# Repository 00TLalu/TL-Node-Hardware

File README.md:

# TL-Node-Hardware
 PCB for OpenTANI

## Spesification
- TL-S2 (ESP32-S2)
- 2 External LDO
- 6 port 4 pin JST-PH Sensor
- 1 port 2 pin JST-PH Battery
- 1 port 2 pin JST-SH Buzzer
- 1 port 4 pin JST-SH I2C
- 1 port 6 pin JST-SH UART
- 1 port 6 pin JST-SH JTAG/SPI
- 2 Reed Switch
- 2 pcs Battery 18650 Battery
- 1 Programeble LED
- 1 Power Switch
- Voltage/Battery Monitor
- MPU-6050 (Optional)

## Schematic

## 3D Model

## PCB

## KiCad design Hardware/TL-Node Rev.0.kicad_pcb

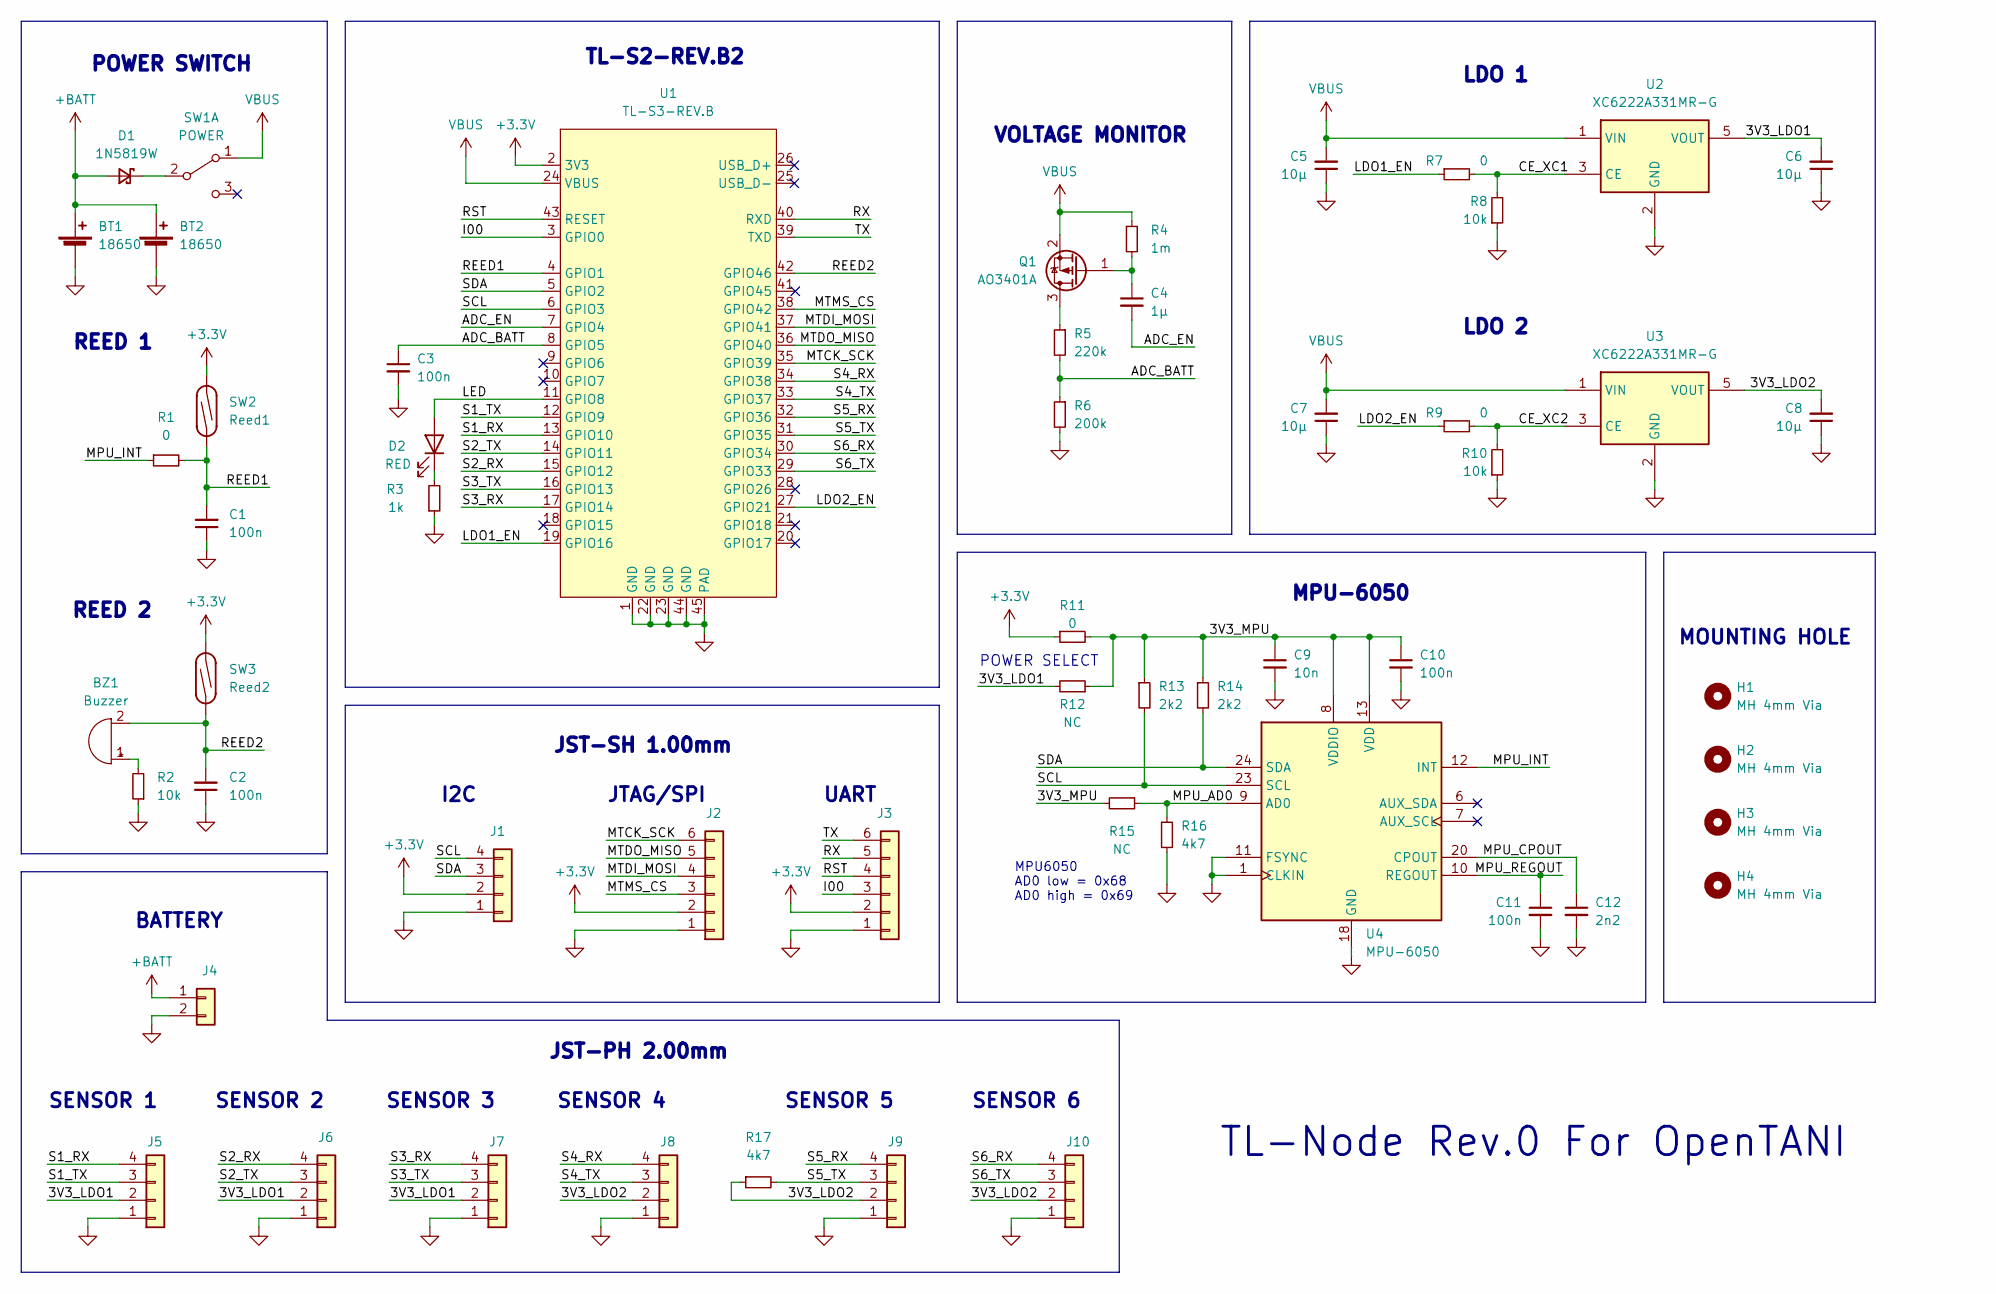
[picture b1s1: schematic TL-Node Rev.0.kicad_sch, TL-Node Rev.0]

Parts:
BT1, BT2: 18650; BatteryHolder_MPD_BH-18650-PC2
BZ1: Buzzer; JST_SH_BM02B-SRSS-TB_1x02-1MP_P1.00mm_Vertical
C1, C2, C3, C10, C11: 100n; C_0402_TL
C4: 1µ; C_0402_TL
C5, C6, C7, C8: 10µ; C_0603_TL
C9: 10n; C_0402_TL
C12: 2n2; C_0402_TL
D1: 1N5819W; D_SOD-123F
D2: RED; D_0603_TL
H1, H2, H3, H4: MH 4mm Via; MountingHole_3mm_Pad_Via
J1: JST-PH 1x04; JST_SH_BM04B-SRSS-TB_1x04-1MP_P1.00mm_Vertical_TL
J2, J3: JST-SH 1x06; JST_SH_1x06-1MP_P1.00mm_Vertical_TL
J4: JST-PH 1x02; JST_PH_B2B-PH-TL-2.0
J5, J6, J7, J8, J9, J10: JST-PH 1x04; JST_PH_S4B-PH-SM4-TB_1x04-1MP_P2.00mm_Horizontal
Q1: AO3401A; SOT-23_TL
R1, R7, R9, R11: 0; R_0402_TL
R2, R8, R10: 10k; R_0402_TL
R3: 1k; R_0402_TL
R4: 1m; R_0402_TL
R5: 220k; R_0402_TL
R6: 200k; R_0402_TL
R12, R15: NC; R_0402_TL
R13, R14: 2k2; R_0402_TL
R16, R17: 4k7; R_0402_TL
SW1: POWER; SW_SPDT_PCM12_TL
SW2: Reed1; SW_SPST_REED_CT10-XXXX-G1
SW3: Reed2; SW_SPST_REED_CT10-XXXX-G1
U1: TL-S3-REV.B; TL-S2_Rev.B2
U2, U3: XC6222A331MR-G; SOT-23-5_TL
U4: MPU-6050; InvenSense_QFN-24_4x4mm_P0.5mm_NoMask

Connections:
+3.3V: J1.2, J2.2, J3.2, R11.1, SW2.1, SW3.1, U1.2 (3V3)
+BATT: BT1.1 (+), BT2.1 (+), D1.2 (A), J4.1
/3V3_LDO1: C6.2, J5.2, J6.2, J7.2, R12.2, U2.5 (VOUT)
/3V3_LDO2: C8.2, J8.2, J9.2, J10.2, R17.1, U3.5 (VOUT)
/3V3_MPU: C9.1, C10.1, R11.2, R12.1, R13.1, R14.1, R15.2, U4.8 (VDDIO), U4.13 (VDD)
/ADC_BATT: C3.1, R5.2, R6.1, U1.8 (GPIO5)
/ADC_EN: C4.2, U1.7 (GPIO4)
/I00: J3.3, U1.3 (GPIO0)
/LDO1_EN: R7.1, U1.19 (GPIO16)
/LDO2_EN: R9.1, U1.27 (GPIO21)
/LED: D2.2 (A), U1.11 (GPIO8)
/MPU_AD0: R15.1, R16.1, U4.9 (AD0)
/MPU_CPOUT: C12.1, U4.20 (CPOUT)
/MPU_INT: R1.1, U4.12 (INT)
/MPU_REGOUT: C11.1, U4.10 (REGOUT)
/MTCK_SCK: J2.6, U1.35 (GPIO39)
/MTDI_MOSI: J2.4, U1.37 (GPIO41)
/MTDO_MISO: J2.5, U1.36 (GPIO40)
/MTMS_CS: J2.3, U1.38 (GPIO42)
/REED1: C1.2, R1.2, SW2.2, U1.4 (GPIO1)
/REED2: BZ1.2 (+), C2.2, SW3.2, U1.42 (GPIO46)
/RST: J3.4, U1.43 (RESET)
/RX: J3.5, U1.40 (RXD)
/S1_RX: J5.4, U1.13 (GPIO10)
/S1_TX: J5.3, U1.12 (GPIO9)
/S2_RX: J6.4, U1.15 (GPIO12)
/S2_TX: J6.3, U1.14 (GPIO11)
/S3_RX: J7.4, U1.17 (GPIO14)
/S3_TX: J7.3, U1.16 (GPIO13)
/S4_RX: J8.4, U1.34 (GPIO38)
/S4_TX: J8.3, U1.33 (GPIO37)
/S5_RX: J9.4, U1.32 (GPIO36)
/S5_TX: J9.3, R17.2, U1.31 (GPIO35)
/S6_RX: J10.4, U1.30 (GPIO34)
/S6_TX: J10.3, U1.29 (GPIO33)
/SCL: J1.4, R13.2, U1.6 (GPIO3), U4.23 (SCL)
/SDA: J1.3, R14.2, U1.5 (GPIO2), U4.24 (SDA)
/TX: J3.6, U1.39 (TXD)
GND: BT1.2 (-), BT2.2 (-), C1.1, C2.1, C3.2, C5.1, C6.1, C7.1, C8.1, C9.2, C10.2, C11.2, C12.2, J1.1, J2.1, J3.1, J4.2, J5.1, J6.1, J7.1, J8.1, J9.1, J10.1, R2.1, R3.1, R6.2, R8.1, R10.1, R16.2, U1.1 (GND), U1.22 (GND), U1.23 (GND), U1.44 (GND), U1.45 (PAD), U2.2 (GND), U3.2 (GND), U4.1 (CLKIN), U4.11 (FSYNC), U4.18 (GND)
unnamed: BZ1.1 (-), R2.2
unnamed: C4.1, Q1.1 (G), R4.2
unnamed: D1.1 (K), SW1.2 (B)
unnamed: D2.1 (K), R3.2
unnamed: Q1.3 (D), R5.1
unnamed: R7.2, R8.2, U2.3 (CE)
unnamed: R9.2, R10.2, U3.3 (CE)
VBUS: C5.2, C7.2, Q1.2 (S), R4.1, SW1.1 (A), U1.24 (VBUS), U2.1 (VIN), U3.1 (VIN)

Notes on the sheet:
LDO 2
TL-S2-REV.B2
SENSOR 4
TL-Node Rev.0 For OpenTANI
SENSOR 5
SENSOR 6
MPU-6050
VOLTAGE MONITOR
REED 1
JTAG/SPI
MOUNTING HOLE
SENSOR 3
MPU6050 AD0 low = 0x68 AD0 high = 0x69
UART
REED 2
BATTERY
POWER SWITCH
JST-PH 2.00mm
JST-SH 1.00mm
SENSOR 1
I2C
POWER SELECT
LDO 1
SENSOR 2

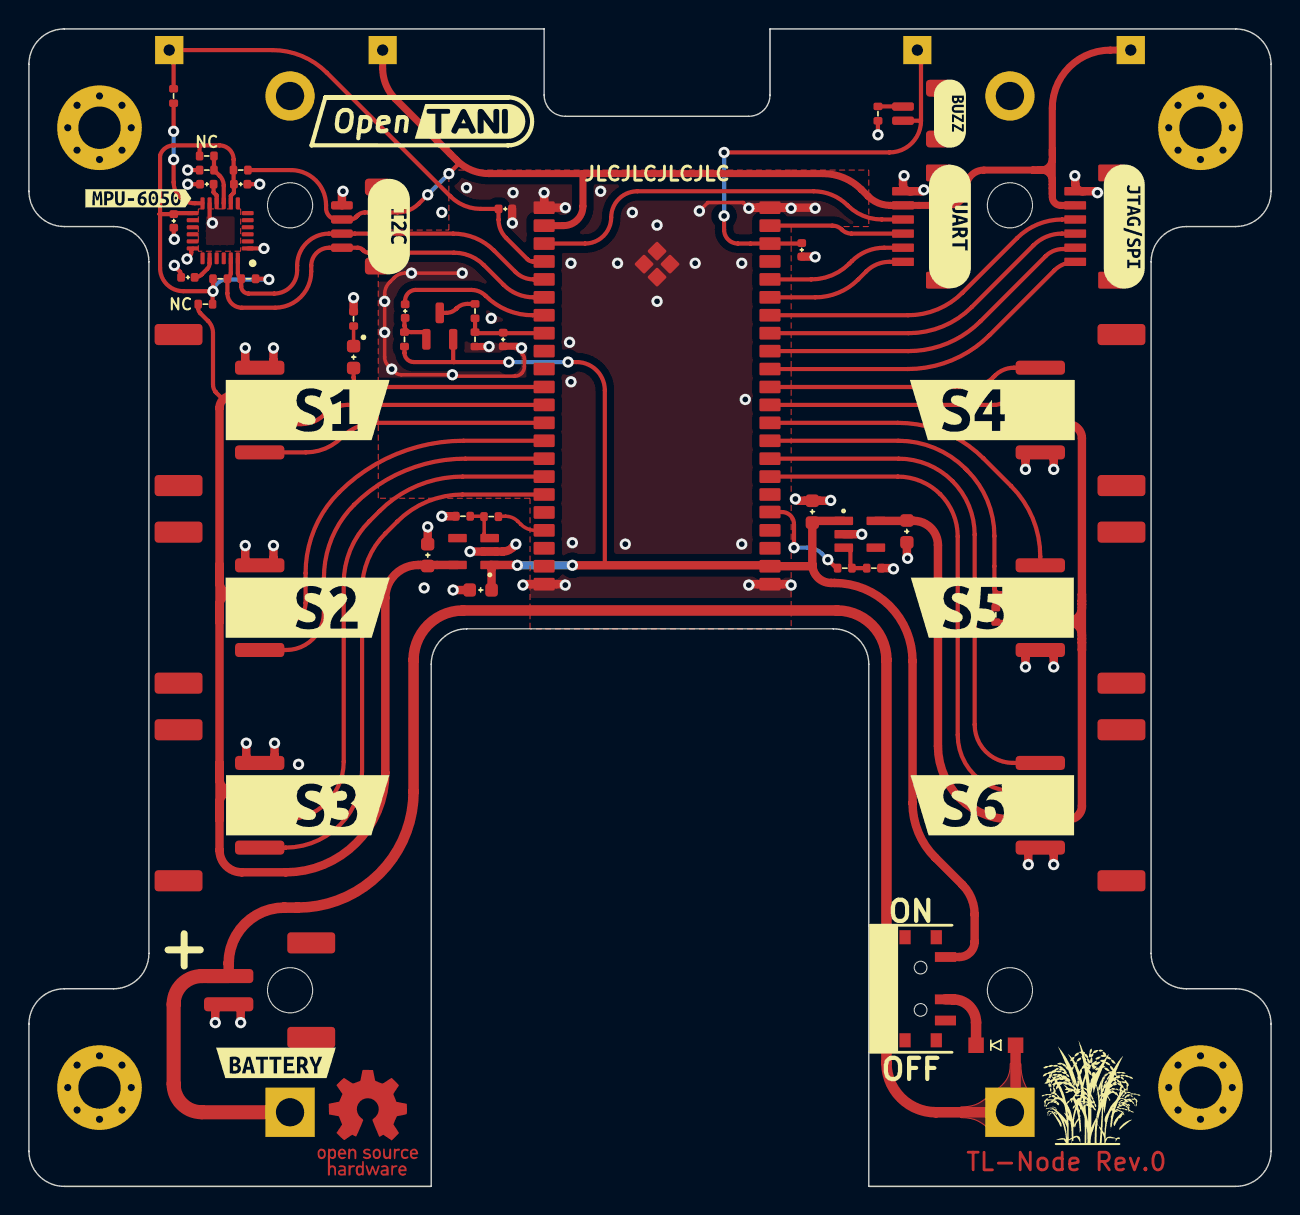
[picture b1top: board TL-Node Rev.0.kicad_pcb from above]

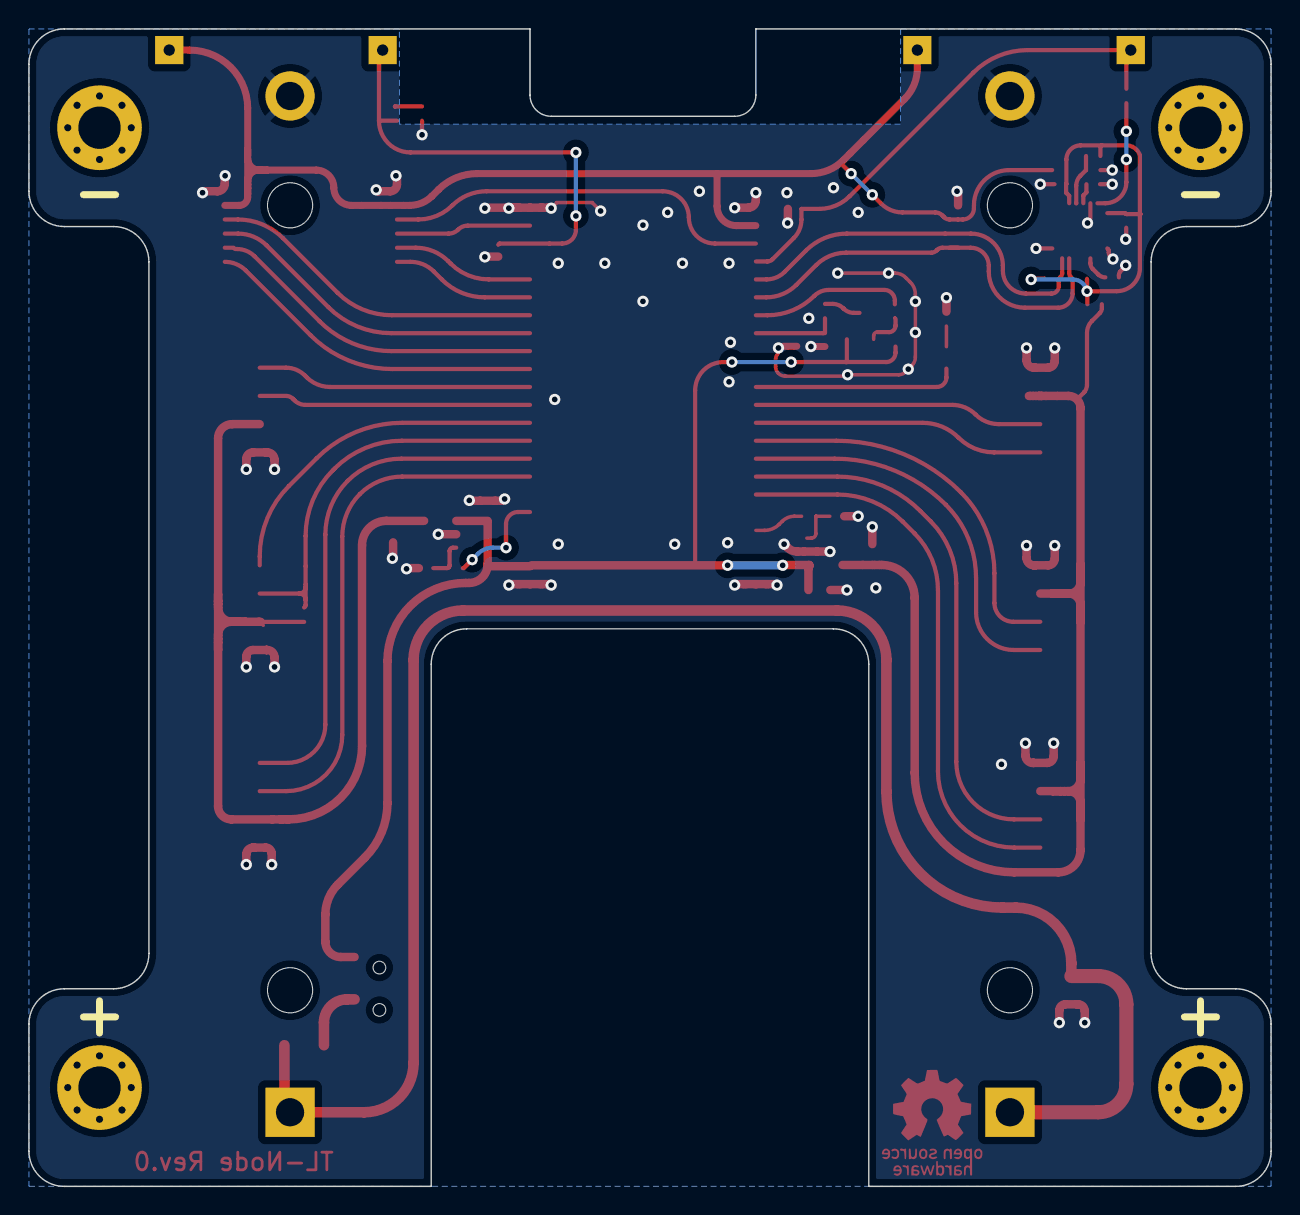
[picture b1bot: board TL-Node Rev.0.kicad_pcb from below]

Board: 2 copper layers, 88.0 x 82.0 mm, 69 parts (2 on the bottom side), 47 nets.

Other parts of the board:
kibuzzard-6343A6AD: G***; kibuzzard-6343A6AD
kibuzzard-6343A6B9: G***; kibuzzard-6343A6B9
kibuzzard-6343A87B: G***; kibuzzard-6343A87B
kibuzzard-6343A88C: G***; kibuzzard-6343A88C
kibuzzard-6343A679: G***; kibuzzard-6343A679
kibuzzard-6343A848: G***; kibuzzard-6343A848
kibuzzard-6343B0FA: G***; kibuzzard-6343B0FA
kibuzzard-6343B22B: G***; kibuzzard-6343B22B
kibuzzard-6343B029: G***; kibuzzard-6343B029
kibuzzard-6343BC66: G***; kibuzzard-6343BC66
kibuzzard-634399EB: G***; kibuzzard-634399EB
kibuzzard-634411D5: G***; kibuzzard-634411D5
kibuzzard-63441851: G***; kibuzzard-63441851

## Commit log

2022-11-02 add hardware
2022-11-04 add pictures
